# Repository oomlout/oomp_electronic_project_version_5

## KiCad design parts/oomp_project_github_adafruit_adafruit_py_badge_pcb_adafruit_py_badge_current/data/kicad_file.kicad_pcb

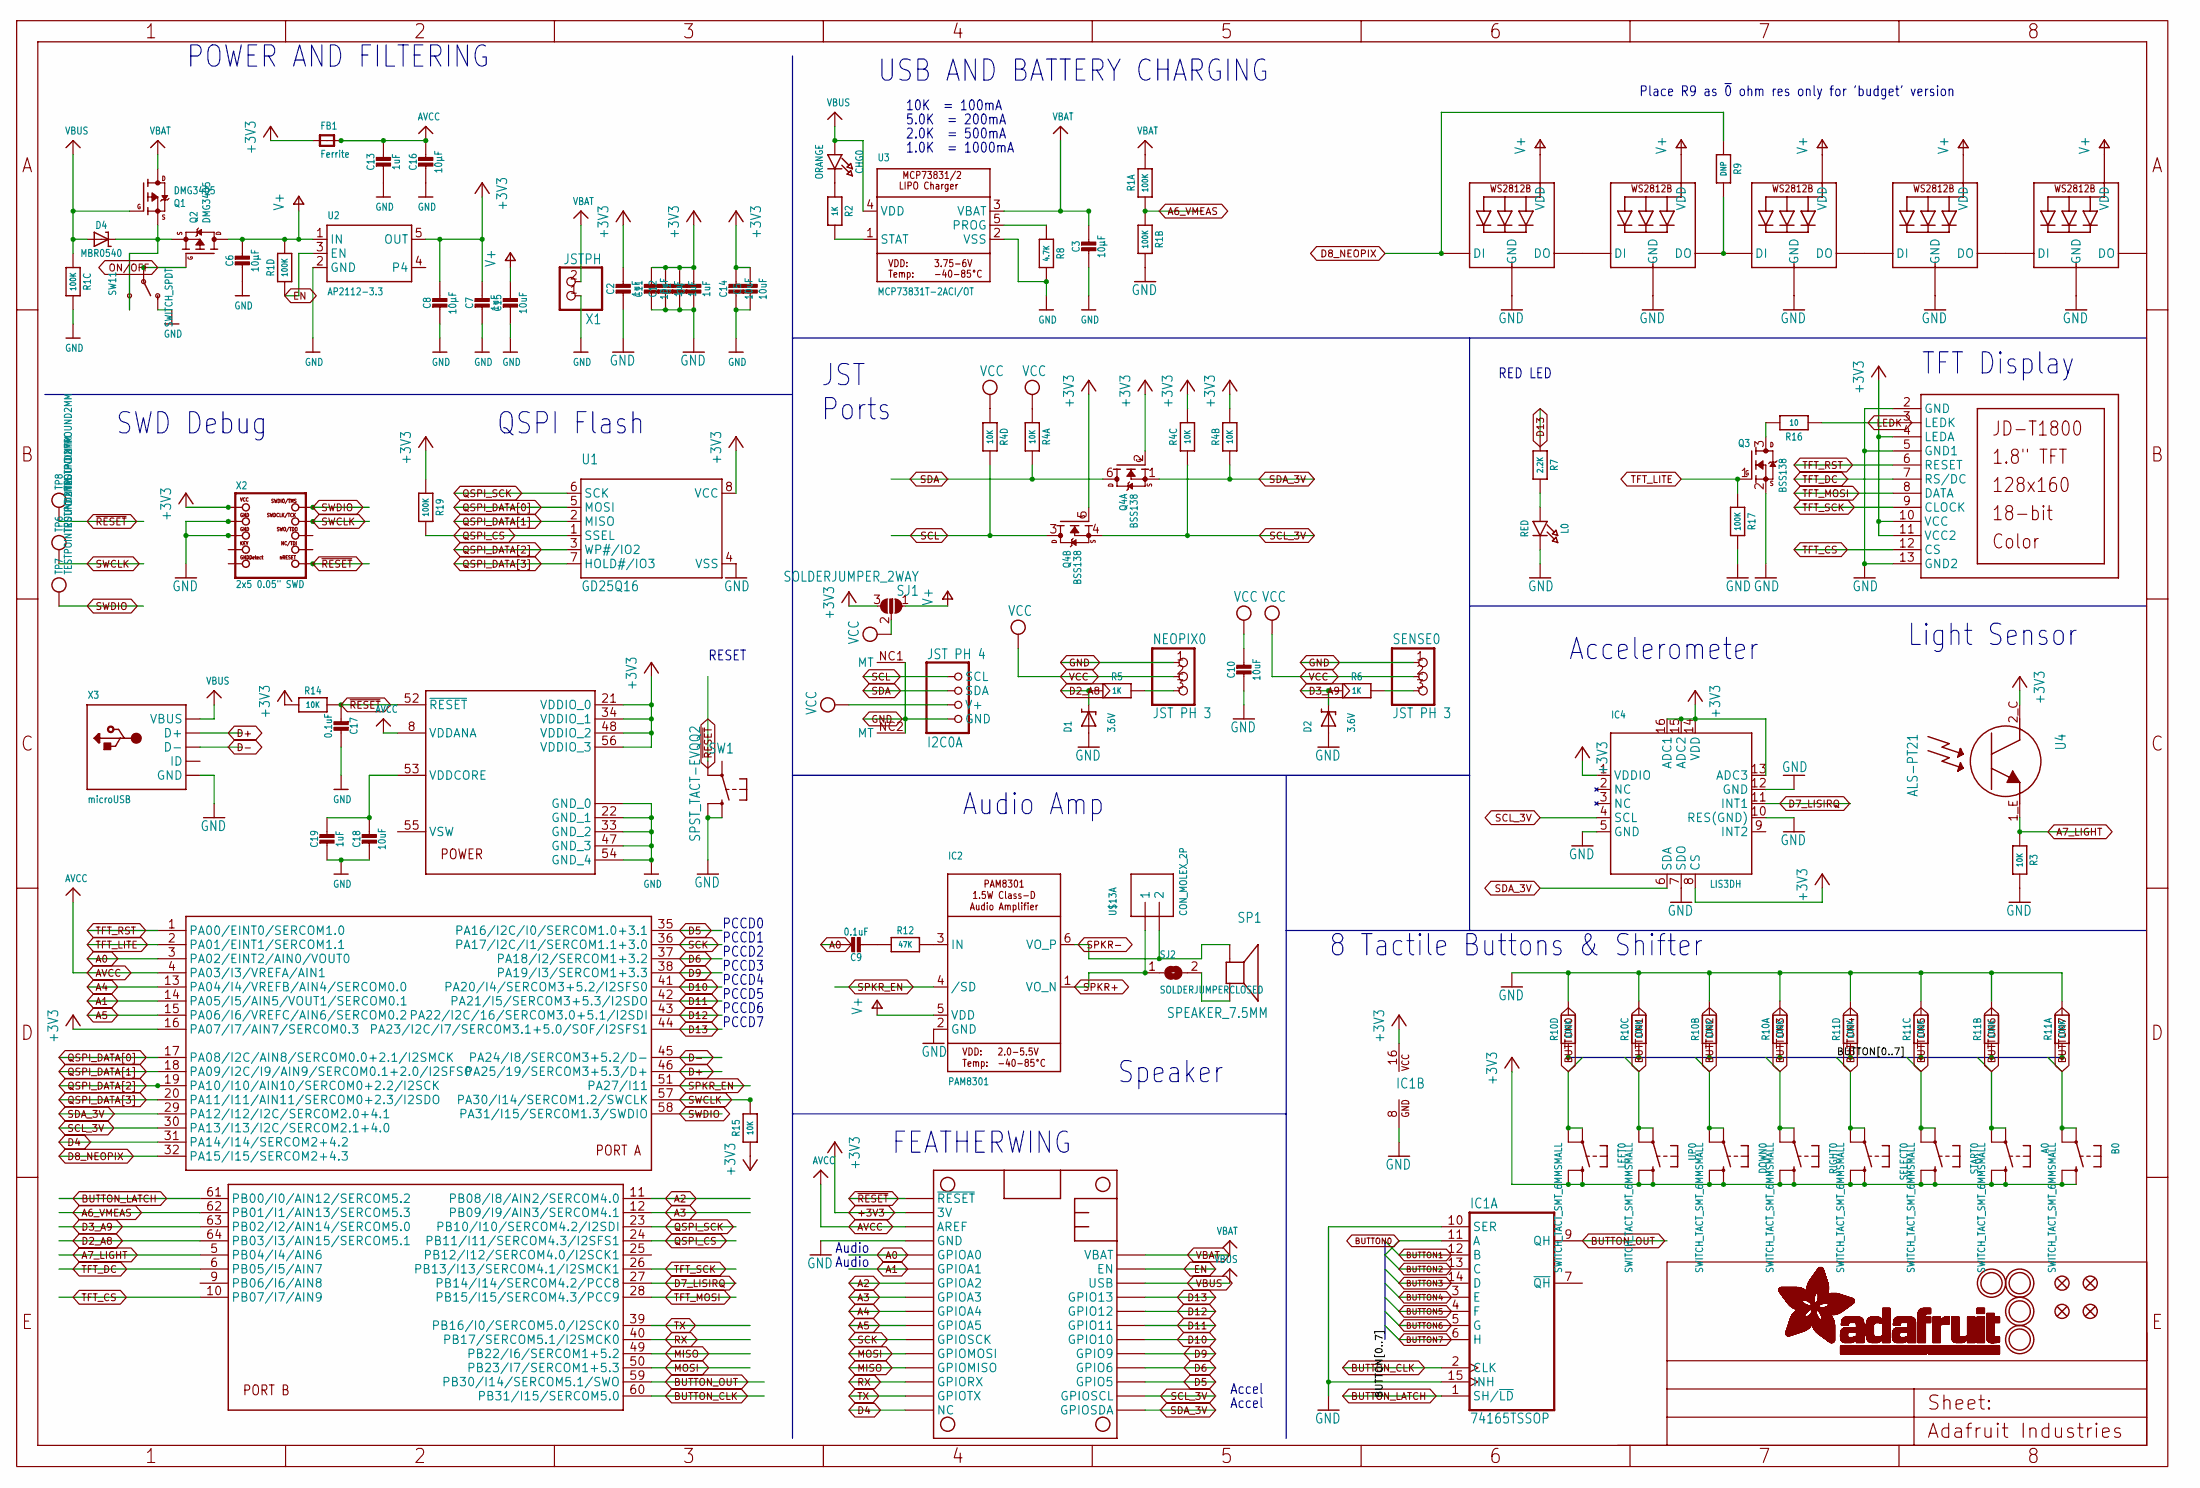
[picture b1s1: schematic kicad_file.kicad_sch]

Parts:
A0: SWITCH_TACT_SMT_6MMSMALL; 6MM_SMT
B0: SWITCH_TACT_SMT_6MMSMALL; 6MM_SMT
C1, C2, C4, C7, C12, C13, C19: 1uF; 0603-NO
C3, C6, C8: 10µF; 0805-NO
C5, C10, C11, C14, C15, C18: 10uF; 0805-NO
C9, C17: 0.1uF; 0603-NO
C16: 10µF; _0805MP
CHG0: ORANGE; CHIPLED_0805_NOOUTLINE
D1, D2: 3.6V; SOD-323
D4: MBR0540; SOD-123
DOWN0: SWITCH_TACT_SMT_6MMSMALL; 6MM_SMT
FB1: Ferrite; 0805-NO
I2C0: JST PH 4; JSTPH4
IC1: 74165TSSOP; TSSOP16
IC2: PAM8301; SOT23-6
IC4: LIS3DH; LGA16_3X3MM
L0: RED; CHIPLED_0805_NOOUTLINE
LCD1: DISP_LCD_JDT1800; JD-T1800
LED1, LED2, LED3, LED4, LED5: WS2812B3535; LED3535
LEFT0: SWITCH_TACT_SMT_6MMSMALL; 6MM_SMT
MS1: FEATHERWING_SMTDUALNOHOLES; FEATHERWING_SMT_NOHOLES
NEOPIX0: JST PH 3; JSTPH3
Q1, Q2: DMG3405; SOT23-R
Q3: BSS138; SOT23-WIDE
Q4: BSS138; SOT363
R1, R10, R11: 100K; RESPACK_4X0603
R2, R5, R6: 1K; 0603-NO
R3, R14, R15: 10K; 0603-NO
R4: 10K; RESPACK_4X0603
R7: 2.2K; 0603-NO
R8: 4.7K; 0603-NO
R9: DNP; 0603-NO
R12: 47K; 0603-NO
R16: 10; 0603-NO
R17, R19: 100K; 0603-NO
RIGHT0: SWITCH_TACT_SMT_6MMSMALL; 6MM_SMT
SELECT0: SWITCH_TACT_SMT_6MMSMALL; 6MM_SMT
SENSE0: JST PH 3; JSTPH3
SJ1: SOLDERJUMPER_2WAY; SOLDERJUMPER_2WAY_OPEN_NOPASTE
SJ2: SOLDERJUMPERCLOSED; SOLDERJUMPER_CLOSEDWIRE
SP1: SPEAKER_7.5MM; BUZZER_SMT_7.5MM
START0: SWITCH_TACT_SMT_6MMSMALL; 6MM_SMT
SW1: SPST_TACT-EVQQ2; EVQ-Q2_SMALLER
SW11: SWITCH_SPDT; SPDT_SMT_SSSS811101
TP6, TP7, TP8: TESTPOINTROUND2MM; TESTPOINT_ROUND_2MM
U1: GD25Q16; SOIC8_208MIL
U2: AP2112-3.3; SOT23-5
U3: MCP73831T-2ACI/OT; SOT23-5
U4: ALS-PT21; ALS-PT26-21C
U$5, U$6, U$15, U$17: MOUNTINGHOLE3.0THIN; MOUNTINGHOLE_3.0_PLATEDTHIN
U$13: CON_MOLEX_2P; 53398-0271
U$24: ATSAMD51J19; PQFN64-1
U$34, U$35, U$42, U$43: FIDUCIAL_1MM
UP0: SWITCH_TACT_SMT_6MMSMALL; 6MM_SMT
X1: JSTPH; JSTPH2
X2: 2x5 0.05" SWD; 2X05_1.27MM_BOX_POSTS
X3: microUSB; 4UCONN_20329_V2

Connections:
+3V3: A0.B (S), A0.B' (S1), B0.B (S), B0.B' (S1), C1.1, C2.1, C4.1, C5.1, C7.1, C8.1, C11.1, C12.1, C14.1, DOWN0.B (S), DOWN0.B' (S1), FB1.1, IC1.16 (VCC), IC4.1 (VDDIO), IC4.8 (CS), IC4.13 (ADC3), IC4.14 (VDD), IC4.15 (ADC2), IC4.16 (ADC1), LCD1.4 (LEDA), LCD1.10 (VCC), LCD1.11 (VCC2), LEFT0.B (S), LEFT0.B' (S1), MS1.2 (3V), MS1.2B (3V), Q4.2 (G), Q4.5 (G), R4.2 (1), R4.3 (1), R14.1, R15.1, R19.1, RIGHT0.B (S), RIGHT0.B' (S1), SELECT0.B (S), SELECT0.B' (S1), SJ1.3, START0.B (S), START0.B' (S1), U1.8 (VCC), U2.5 (OUT), U4.2_C (C), U$24.16 (PA07/I7/AIN7/SERCOM0.3), U$24.21 (VDDIO_0), U$24.34 (VDDIO_1), U$24.48 (VDDIO_2), U$24.56 (VDDIO_3), UP0.B (S), UP0.B' (S1), X2.1 (VCC)
A0: C9.1, MS1.5 (GPIOA0), MS1.5B (GPIOA0), U$24.3 (PA02/EINT2/AIN0/VOUT0)
A1: MS1.6 (GPIOA1), MS1.6B (GPIOA1), U$24.14 (PA05/I5/AIN5/VOUT1/SERCOM0.1)
A2: MS1.7 (GPIOA2), MS1.7B (GPIOA2), U$24.11 (PB08/I8/AIN2/SERCOM4.0)
A3: MS1.8 (GPIOA3), MS1.8B (GPIOA3), U$24.12 (PB09/I9/AIN3/SERCOM4.1)
A4: MS1.9 (GPIOA4), MS1.9B (GPIOA4), U$24.13 (PA04/I4/VREFB/AIN4/SERCOM0.0)
A5: MS1.10 (GPIOA5), MS1.10B (GPIOA5), U$24.15 (PA06/I6/VREFC/AIN6/SERCOM0.2)
A6_VMEAS: R1.1, R1.2 (1), U$24.62 (PB01/I1/AIN13/SERCOM5.3)
A7_LIGHT: R3.2, U4.1_E (E), U$24.5 (PB04/I4/AIN6)
AVCC: C13.1, C16.1, FB1.2, MS1.3 (AREF), MS1.3B (AREF), U$24.4 (PA03/I3/VREFA/AIN1), U$24.8 (VDDANA)
BUTTON0: IC1.11 (A), LEFT0.A, LEFT0.A' (P1), R10.4 (1)
BUTTON1: IC1.12 (B), R10.3 (1), UP0.A, UP0.A' (P1)
BUTTON2: DOWN0.A, DOWN0.A' (P1), IC1.13 (C), R10.2 (1)
BUTTON3: IC1.14 (D), R10.1, RIGHT0.A, RIGHT0.A' (P1)
BUTTON4: IC1.3 (E), R11.4 (1), SELECT0.A, SELECT0.A' (P1)
BUTTON5: IC1.4 (F), R11.3 (1), START0.A, START0.A' (P1)
BUTTON6: A0.A, A0.A' (P1), IC1.5 (G), R11.2 (1)
BUTTON7: B0.A, B0.A' (P1), IC1.6 (H), R11.1
BUTTON_CLK: IC1.2 (CLK), U$24.60 (PB31/I15/SERCOM5.0)
BUTTON_LATCH: IC1.1 (SH/~LD), U$24.61 (PB00/I0/AIN12/SERCOM5.2)
BUTTON_OUT: IC1.9 (QH), U$24.59 (PB30/I14/SERCOM5.1/SWO)
CHG_LED: R2.2, U3.1 (STAT)
CHG_RATE: R8.1, U3.5 (PROG)
D2_: NEOPIX0.3, R5.1
D2_A8: D1.C, R5.2, U$24.64 (PB03/I3/AIN15/SERCOM5.1)
D3_: R6.1, SENSE0.3
D3_A9: D2.C, R6.2, U$24.63 (PB02/I2/AIN14/SERCOM5.0)
D4: MS1.16 (NC), MS1.16B (NC), U$24.31 (PA14/I14/SERCOM2+4.2)
D5: MS1.19 (GPIO5), MS1.19B (GPIO5), U$24.35 (PA16/I2C/I0/SERCOM1.0+3.1)
D6: MS1.20 (GPIO6), MS1.20B (GPIO6), U$24.37 (PA18/I2/SERCOM1+3.2)
D7_LISIRQ: IC4.11 (INT1), U$24.27 (PB14/I14/SERCOM4.2/PCC8)
D8_NEOPIX: LED1.1 (DI), R9.1, U$24.32 (PA15/I15/SERCOM2+4.3)
D9: MS1.21 (GPIO9), MS1.21B (GPIO9), U$24.38 (PA19/I3/SERCOM1+3.3)
D10: MS1.22 (GPIO10), MS1.22B (GPIO10), U$24.41 (PA20/I4/SERCOM3+5.2/I2SFS0)
D11: MS1.23 (GPIO11), MS1.23B (GPIO11), U$24.42 (PA21/I5/SERCOM3+5.3/I2SDO)
D12: MS1.24 (GPIO12), MS1.24B (GPIO12), U$24.43 (PA22/I2C/16/SERCOM3.0+5.1/I2SDI)
D13: MS1.25 (GPIO13), MS1.25B (GPIO13), R7.1, U$24.44 (PA23/I2C/I7/SERCOM3.1+5.0/SOF/I2SFS1)
D+: U$24.46 (PA25/19/SERCOM3+5.3/D+), X3.D+
D-: U$24.45 (PA24/I8/SERCOM3+5.2/D-), X3.D-
EN: MS1.27 (EN), MS1.27B (EN), R1.4 (1), U2.3 (EN)
GND: C1.2, C2.2, C3.2, C4.2, C5.2, C6.2, C7.2, C8.2, C10.2, C11.2, C12.2, C13.2, C14.2, C15.2, C16.2, C17.1, C18.2, C19.2, D1.A, D2.A, I2C0.1 (GND), I2C0.NC1 (MT), I2C0.NC2 (MT), IC1.8 (GND), IC1.10 (SER), IC1.15 (INH), IC2.2 (GND), IC4.5 (GND), IC4.7 (SDO), IC4.10 (RES(GND)), IC4.12 (GND), L0.C, LCD1.2 (GND), LCD1.5 (GND1), LCD1.13 (GND2), LED1.4 (GND), LED2.4 (GND), LED3.4 (GND), LED4.4 (GND), LED5.4 (GND), MS1.4 (GND), MS1.4B (GND), NEOPIX0.1, Q3.2 (S), R1.6 (2), R1.7 (2), R3.1, R8.2, R10.5 (2), R10.6 (2), R10.7 (2), R10.8 (2), R11.5 (2), R11.6 (2), R11.7 (2), R11.8 (2), R17.2, SENSE0.1, SW1.B (S), SW1.B' (S1), SW11.A (O), U1.4 (VSS), U2.2 (GND), U3.2 (VSS), U$24.7 (GND_0), U$24.22 (GND_1), U$24.33 (GND_2), U$24.47 (GND_3), U$24.54 (GND_4), U$24.EXP (GND_0), X1.1, X2.3 (GND), X2.5 (GND), X3.BASE@1 (GND), X3.BASE@2 (GND), X3.GND, X3.SPRT@1 (GND), X3.SPRT@2 (GND), X3.SPRT@3 (GND), X3.SPRT@4 (GND)
LEDK: LCD1.3 (LEDK), R16.1
MISO: MS1.13 (GPIOMISO), MS1.13B (GPIOMISO), U$24.49 (PB22/I6/SERCOM1+5.2)
MOSI: MS1.12 (GPIOMOSI), MS1.12B (GPIOMOSI), U$24.50 (PB23/I7/SERCOM1+5.3)
unnamed: CHG0.C, R2.1
unnamed: L0.A, R7.2
unnamed: LED1.3 (DO), LED2.1 (DI)
unnamed: LED2.3 (DO), LED3.1 (DI), R9.2
unnamed: LED3.3 (DO), LED4.1 (DI)
unnamed: Q3.3 (D), R16.2
unnamed: LED4.3 (DO), LED5.1 (DI)
unnamed: D4.C, Q1.2 (S), Q2.2 (S), SW11.C (S)
unnamed: C9.2, R12.1
unnamed: IC2.3 (IN), R12.2
unnamed: SJ2.2, SP1.-
ON/OFF: Q2.1 (G), SW11.B
QSPI_CS: R19.2, U1.1 (SSEL), U$24.24 (PB11/I11/SERCOM4.3/I2SFS1)
QSPI_DATA[0]: U1.5 (MOSI), U$24.17 (PA08/I2C/AIN8/SERCOM0.0+2.1/I2SMCK)
QSPI_DATA[1]: U1.2 (MISO), U$24.18 (PA09/I2C/I9/AIN9/SERCOM0.1+2.0/I2SFS0)
QSPI_DATA[2]: U1.3 (WP#/IO2), U$24.19 (PA10/I10/AIN10/SERCOM0+2.2/I2SCK)
QSPI_DATA[3]: U1.7 (HOLD#/IO3), U$24.20 (PA11/I11/AIN11/SERCOM0+2.3/I2SDO)
QSPI_SCK: U1.6 (SCK), U$24.23 (PB10/I10/SERCOM4.2/I2SDI)
RX: MS1.14 (GPIORX), MS1.14B (GPIORX), U$24.40 (PB17/SERCOM5.1/I2SMCK0)
SCK: MS1.11 (GPIOSCK), MS1.11B (GPIOSCK), U$24.36 (PA17/I2C/I1/SERCOM1.1+3.0)
SCL: I2C0.4 (SCL), Q4.3 (D), R4.5 (2)
SCL_3V: IC4.4 (SCL), MS1.18 (GPIOSCL), MS1.18B (GPIOSCL), Q4.4 (S), R4.6 (2), U$24.30 (PA13/I13/I2C/SERCOM2.1+4.0)
SDA: I2C0.3 (SDA), Q4.6 (D), R4.8 (2)
SDA_3V: IC4.6 (SDA), MS1.17 (GPIOSDA), MS1.17B (GPIOSDA), Q4.1 (S), R4.7 (2), U$24.29 (PA12/I12/I2C/SERCOM2.0+4.1)
SPKR+: IC2.1 (VO_N), SJ2.1, U$13.1
SPKR-: IC2.6 (VO_P), SP1.+, U$13.2
SPKR_EN: IC2.4 (/SD), U$24.51 (PA27/I11)
SWCLK: R15.2, TP6.P$1, U$24.57 (PA30/I14/SERCOM1.2/SWCLK), X2.4 (SWDCLK)
SWDIO: TP7.P$1, U$24.58 (PA31/I15/SERCOM1.3/SWDIO), X2.2 (SWDIO)
TFT_CS: LCD1.12 (CS), U$24.10 (PB07/I7/AIN9)
TFT_DC: LCD1.7 (RS/DC), U$24.6 (PB05/I5/AIN7)
TFT_LITE: Q3.1 (G), R17.1, U$24.2 (PA01/EINT1/SERCOM1.1)
TFT_MOSI: LCD1.8 (DATA), U$24.28 (PB15/I15/SERCOM4.3/PCC9)
TFT_RST: LCD1.6 (RESET), U$24.1 (PA00/EINT0/SERCOM1.0)
TFT_SCK: LCD1.9 (CLOCK), U$24.26 (PB13/I13/SERCOM4.1/I2SMCK1)
TX: MS1.15 (GPIOTX), MS1.15B (GPIOTX), U$24.39 (PB16/I0/SERCOM5.0/I2SCK0)
V+: C6.1, C15.1, IC2.5 (VDD), LED1.2 (VDD), LED2.2 (VDD), LED3.2 (VDD), LED4.2 (VDD), LED5.2 (VDD), Q2.3 (D), R1.5 (2), SJ1.1, U2.1 (IN)
VBAT: C3.1, MS1.28 (VBAT), MS1.28B (VBAT), Q1.3 (D), R1.8 (2), U3.3 (VBAT), X1.2
VBUS: CHG0.A, D4.A, MS1.26 (USB), MS1.26B (USB), Q1.1 (G), R1.3 (1), U3.4 (VDD), X3.VBUS
VCC: C10.1, I2C0.2 (V+), NEOPIX0.2, R4.1, R4.4 (1), SENSE0.2, SJ1.2
VDDCORE2: C18.1, C19.1, U$24.53 (VDDCORE)
~RESET: C17.2, MS1.1 (~RESET), MS1.1B (~RESET), R14.2, SW1.A' (P1), TP8.P$1, U$24.52 (~RESET), X2.10 (NRESET)

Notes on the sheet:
PCCD6
PCCD3
Place R9 as ~{0} ohm res only for 'budget' version
10K = 100mA
PCCD2
SWD Debug
Audio Amp
Accel
QSPI Flash
USB AND BATTERY CHARGING
JST Ports
FEATHERWING
1.0K = 1000mA
Speaker
8 Tactile Buttons & Shifter
5.0K = 200mA
Audio
PCCD5
PCCD7
Light Sensor
2.0K = 500mA
PCCD4
RED LED
PCCD1
Accelerometer
TFT Display
RESET
POWER AND FILTERING
PCCD0

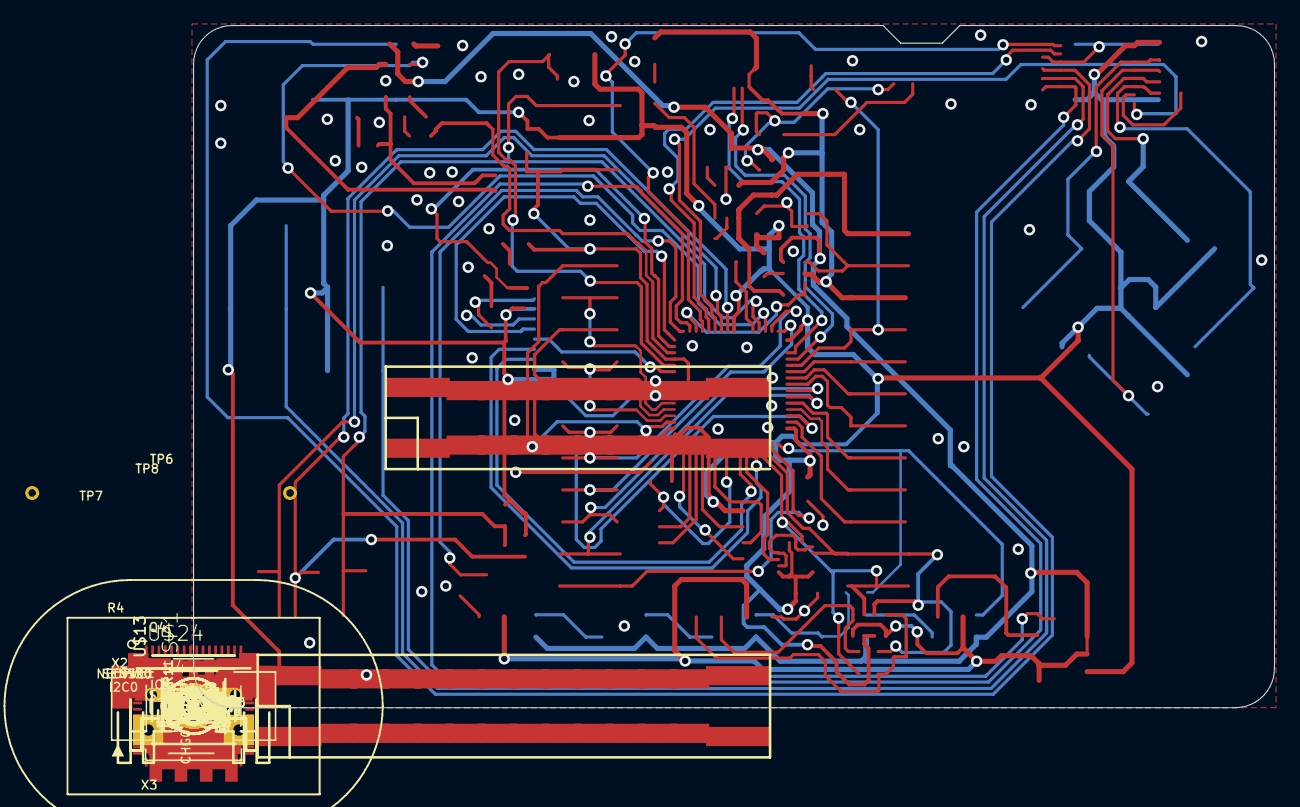
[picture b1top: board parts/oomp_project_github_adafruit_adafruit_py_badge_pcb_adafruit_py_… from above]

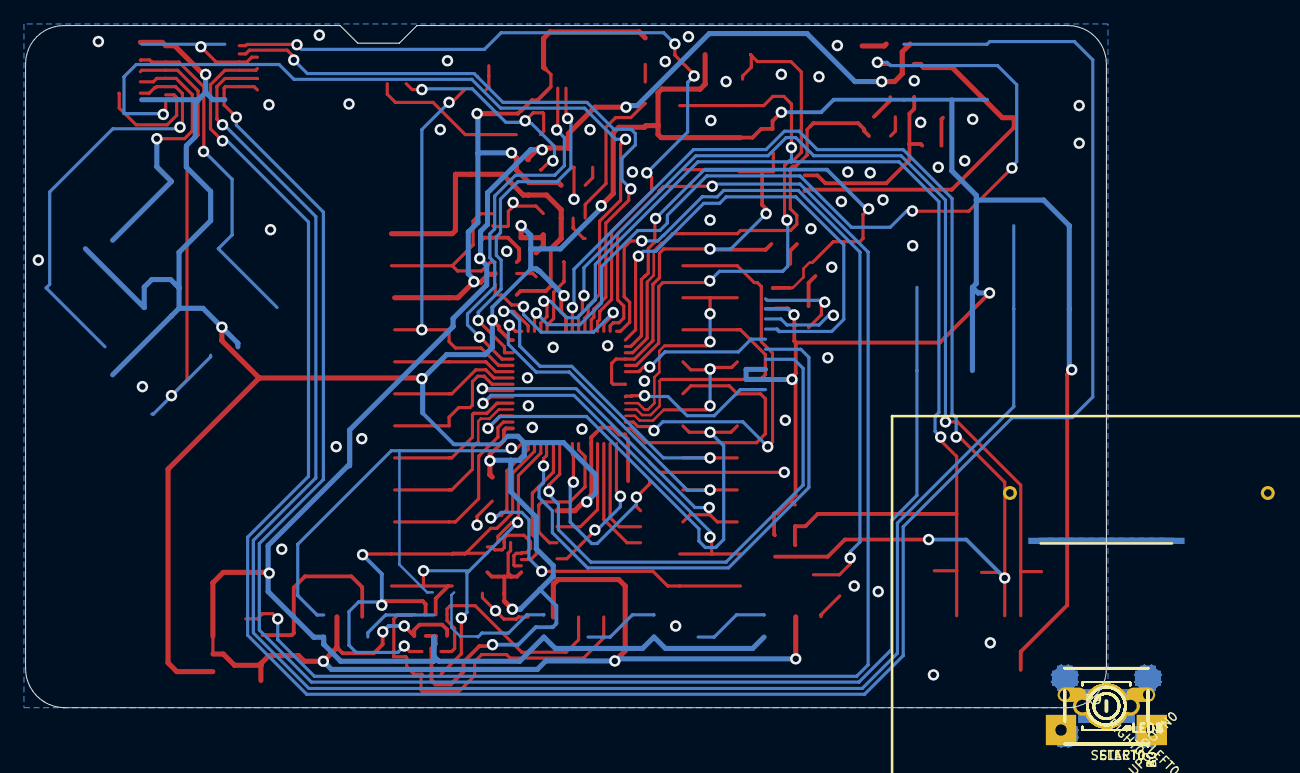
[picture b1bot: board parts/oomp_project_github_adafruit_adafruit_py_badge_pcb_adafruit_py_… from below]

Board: 2 copper layers, 85.7 x 54.1 mm, 96 parts (18 on the bottom side), 86 nets.

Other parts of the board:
U$8: SPEAKER_OVAL8OHM
U$18: PYBADGE_TOP
U$32: PYBADGE_BOT
U$37: PCBFEAT-REV-040

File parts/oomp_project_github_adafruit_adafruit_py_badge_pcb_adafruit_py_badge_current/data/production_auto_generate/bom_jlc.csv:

Comment,Designator,Footprint,LCSC Part #
,"A0,B0,DOWN0,LEFT0,RIGHT0,SELECT0,START0,UP0",Adafruit PyBadge-import-fps:6MM_SMT,
,U$37,Adafruit PyBadge-import-fps:PCBFEAT-REV-040,
,U$32,Adafruit PyBadge-import-fps:PYBADGE_BOT,
,U$18,Adafruit PyBadge-import-fps:PYBADGE_TOP,
,SW11,Adafruit PyBadge-import-fps:SPDT_SMT_SSSS811101,
,U$8,Adafruit PyBadge-import-fps:SPEAKER_OVAL8OHM,
,"TP6,TP7,TP8",Adafruit PyBadge-import-fps:TESTPOINT_ROUND_2MM,
0.1uF,"C9,C17",Adafruit PyBadge-import-fps:0603-NO,C14663
10,R16,Adafruit PyBadge-import-fps:0603-NO,C22859
100K,"R17,R19",Adafruit PyBadge-import-fps:0603-NO,C25803
100K,"R1,R10,R11",Adafruit PyBadge-import-fps:RESPACK_4X0603,C25803
10K,"R3,R14,R15",Adafruit PyBadge-import-fps:0603-NO,C98220
10K,R4,Adafruit PyBadge-import-fps:RESPACK_4X0603,C98220
10uF,"C5,C10,C11,C14,C15,C18",Adafruit PyBadge-import-fps:0805-NO,
10µF,"C3,C6,C8",Adafruit PyBadge-import-fps:0805-NO,
10µF,C16,Adafruit PyBadge-import-fps:_0805MP,
1K,"R2,R5,R6",Adafruit PyBadge-import-fps:0603-NO,C2907002
1uF,"C1,C2,C4,C7,C12,C13,C19",Adafruit PyBadge-import-fps:0603-NO,C5673
2.2K,R7,Adafruit PyBadge-import-fps:0603-NO,C4190
"2x5 0.05"" SWD",X2,Adafruit PyBadge-import-fps:2X05_1.27MM_BOX_POSTS,
3.6V,"D1,D2",Adafruit PyBadge-import-fps:SOD-323,
4.7K,R8,Adafruit PyBadge-import-fps:0603-NO,C23162
47K,R12,Adafruit PyBadge-import-fps:0603-NO,C2907042
74165TSSOP,IC1,Adafruit PyBadge-import-fps:TSSOP16,
ALS-PT21,U4,Adafruit PyBadge-import-fps:ALS-PT26-21C,
AP2112-3.3,U2,Adafruit PyBadge-import-fps:SOT23-5,
ATSAMD51J19,U$24,Adafruit PyBadge-import-fps:PQFN64-1,
BSS138,Q3,Adafruit PyBadge-import-fps:SOT23-WIDE,C52895
BSS138,Q4,Adafruit PyBadge-import-fps:SOT363,
CON_MOLEX_2P,U$13,Adafruit PyBadge-import-fps:53398-0271,
DISP_LCD_JDT1800,LCD1,Adafruit PyBadge-import-fps:JD-T1800,
DMG3405,"Q1,Q2",Adafruit PyBadge-import-fps:SOT23-R,
DNP,R9,Adafruit PyBadge-import-fps:0603-NO,
FEATHERWING_SMTDUALNOHOLES,MS1,Adafruit PyBadge-import-fps:FEATHERWING_SMT_NOHOLES,
Ferrite,FB1,Adafruit PyBadge-import-fps:0805-NO,
FIDUCIAL_1MM,"U$34,U$35,U$42,U$43",Adafruit PyBadge-import-fps:FIDUCIAL_1MM,
GD25Q16,U1,Adafruit PyBadge-import-fps:SOIC8_208MIL,
JST PH 3,"NEOPIX0,SENSE0",Adafruit PyBadge-import-fps:JSTPH3,
JST PH 4,I2C0,Adafruit PyBadge-import-fps:JSTPH4,
JSTPH,X1,Adafruit PyBadge-import-fps:JSTPH2,
LIS3DH,IC4,Adafruit PyBadge-import-fps:LGA16_3X3MM,
MBR0540,D4,Adafruit PyBadge-import-fps:SOD-123,
MCP73831T-2ACI/OT,U3,Adafruit PyBadge-import-fps:SOT23-5,
microUSB,X3,Adafruit PyBadge-import-fps:4UCONN_20329_V2,
ORANGE,CHG0,Adafruit PyBadge-import-fps:CHIPLED_0805_NOOUTLINE,
PAM8301,IC2,Adafruit PyBadge-import-fps:SOT23-6,
RED,L0,Adafruit PyBadge-import-fps:CHIPLED_0805_NOOUTLINE,
SPEAKER_7.5MM,SP1,Adafruit PyBadge-import-fps:BUZZER_SMT_7.5MM,
SPST_TACT-EVQQ2,SW1,Adafruit PyBadge-import-fps:EVQ-Q2_SMALLER,
WS2812B3535,"LED1,LED2,LED3,LED4,LED5",Adafruit PyBadge-import-fps:LED3535,

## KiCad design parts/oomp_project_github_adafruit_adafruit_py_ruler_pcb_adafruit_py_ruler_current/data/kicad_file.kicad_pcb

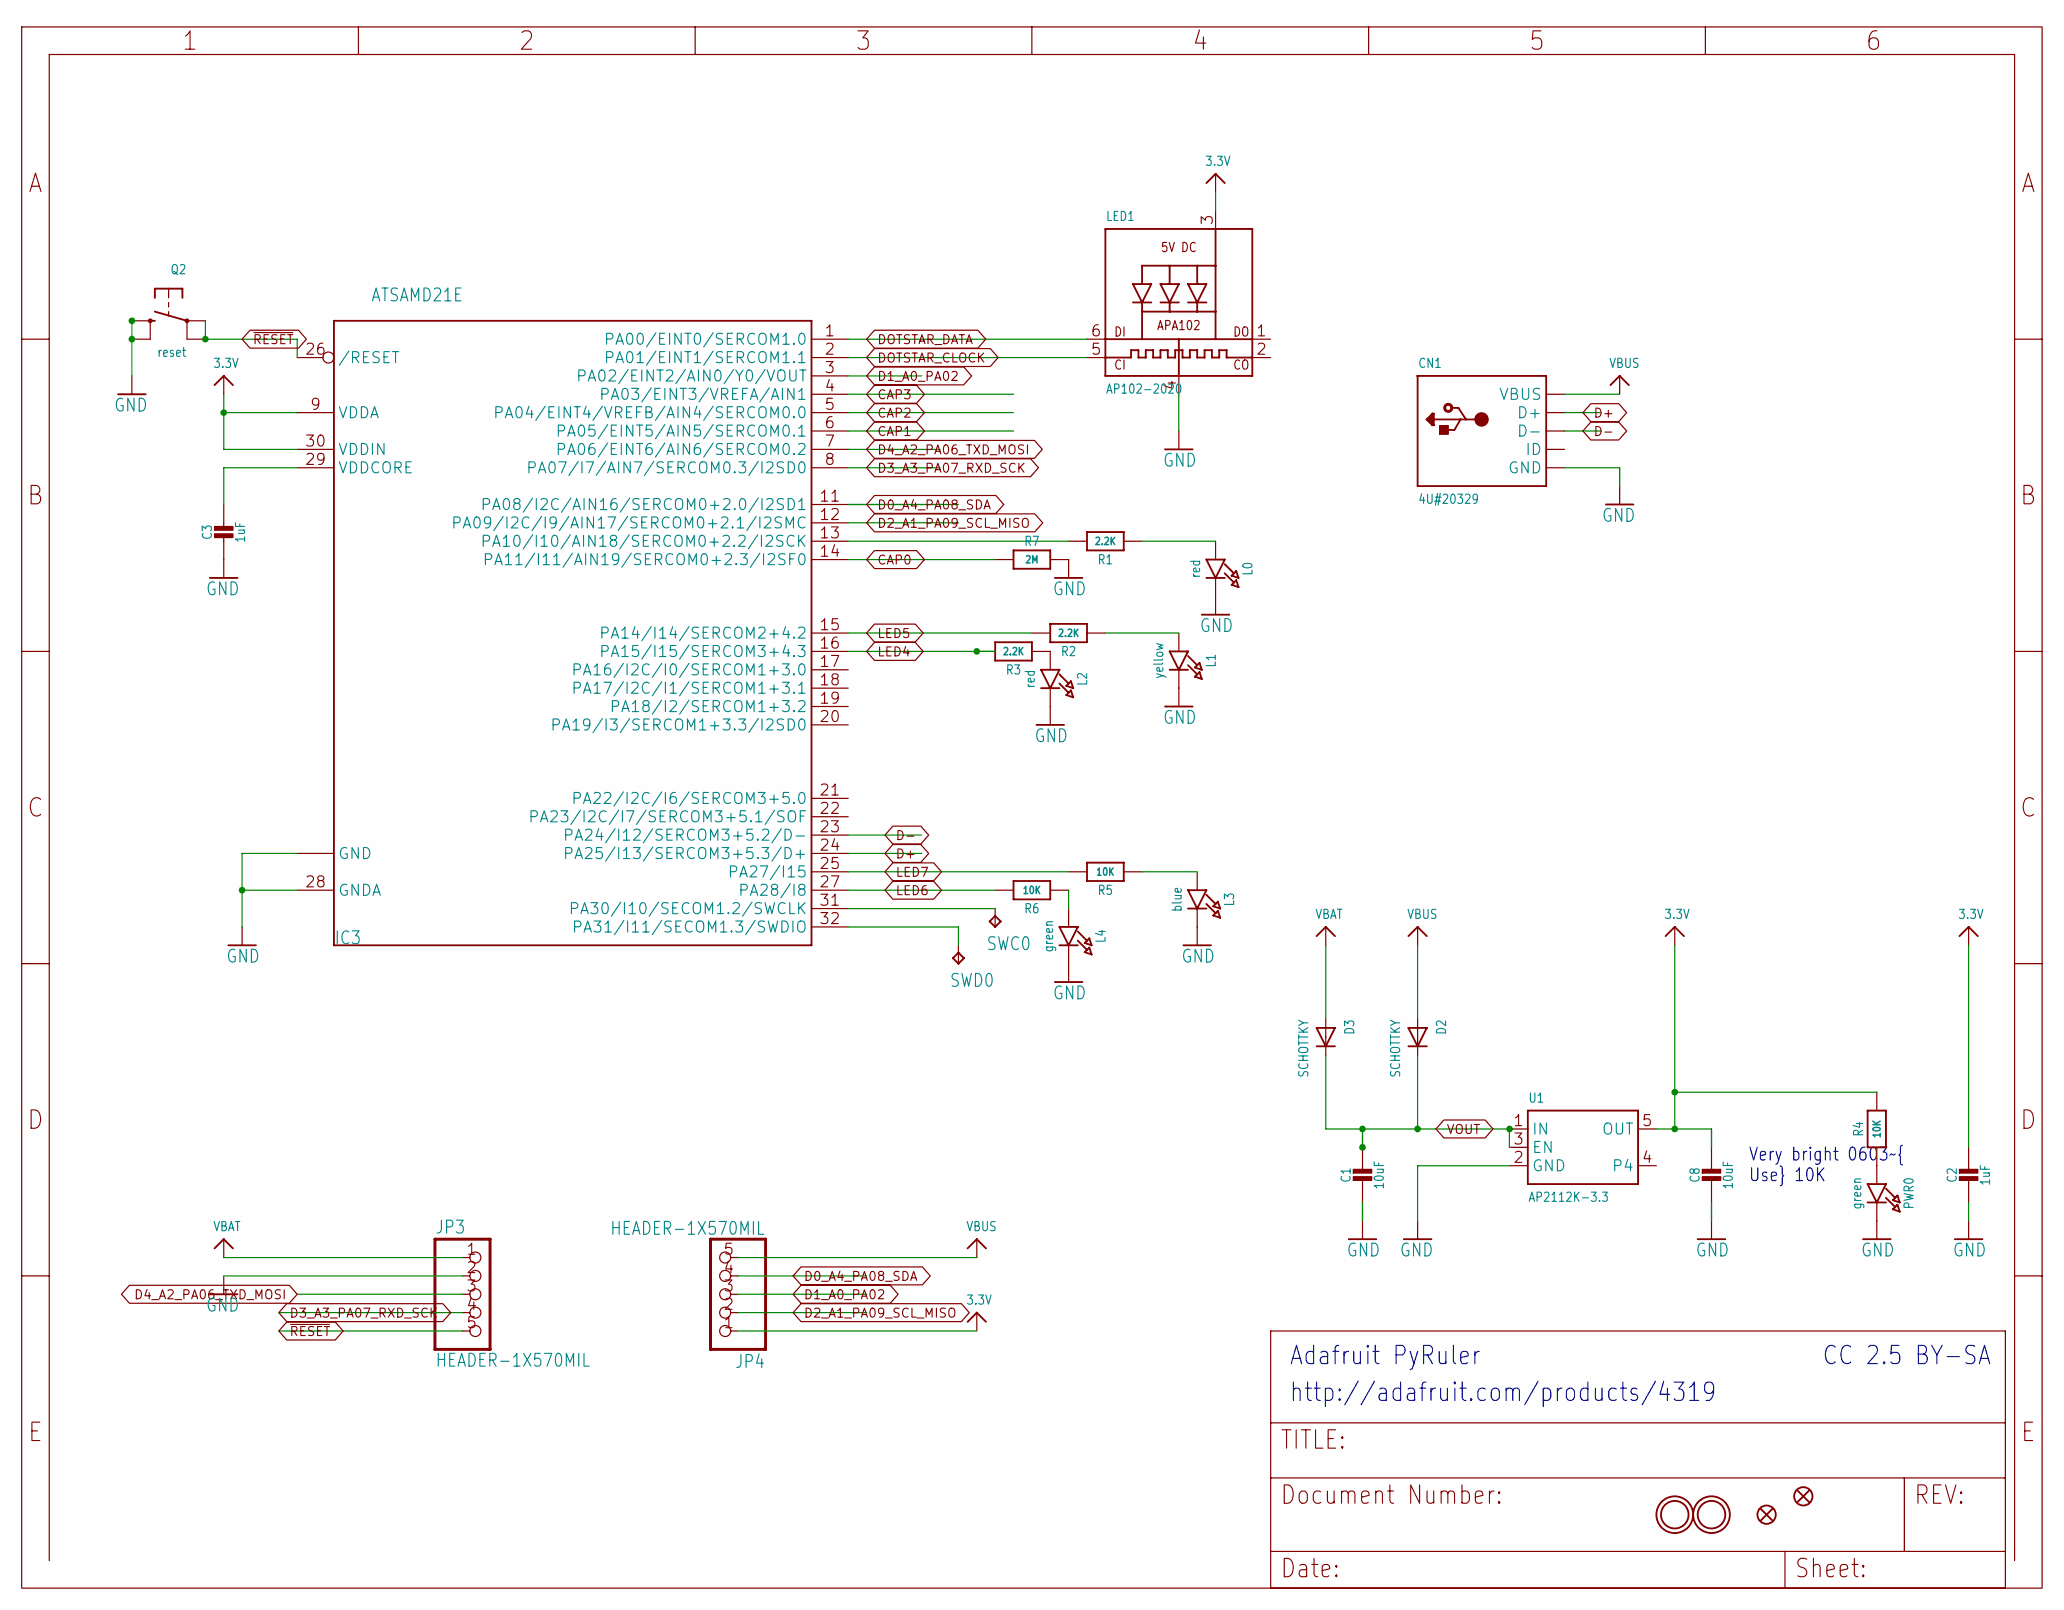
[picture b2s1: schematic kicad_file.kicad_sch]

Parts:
C1, C8: 10uF; 0805-NO
C2, C3: 1uF; 0603-NO
CN1: 4U#20329; 4UCONN_20329_NARROW
D2, D3: SCHOTTKY; SOD-123FL
IC3: ATSAMD21E; QFN32_5MM
JP3, JP4: HEADER-1X570MIL; 1X05_ROUND_70
L0, L2: red; CHIPLED_0603_NOOUTLINE
L1: yellow; CHIPLED_0603_NOOUTLINE
L3: blue; CHIPLED_0603_NOOUTLINE
L4: green; CHIPLED_0603_NOOUTLINE
LED1: AP102-2020; APA102_2020
PWR0: green; CHIPLED_0603_NOOUTLINE
Q2: reset; BTN_KMR2_4.6X2.8
R1, R2, R3: 2.2K; 0603-NO
R4, R5, R6: 10K; 0603-NO
R7: 2M; 0603-NO
SWC0: TPB1,27; B1,27
SWD0: TPB1,27; B1,27
U1: AP2112K-3.3; SOT23-5
U$1, U$6: FIDUCIAL_1MM
U$8, U$9: MOUNTINGHOLE2.0; MOUNTINGHOLE_2.0_PLATED

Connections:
3.3V: C2.1, C8.1, IC3.9 (VDDA), IC3.30 (VDDIN), JP4.1, LED1.3 (VDD), R4.2, U1.5 (OUT)
CAP0: IC3.14 (PA11/I11/AIN19/SERCOM0+2.3/I2SF0), R7.1
CAP1: IC3.6 (PA05/EINT5/AIN5/SERCOM0.1)
CAP2: IC3.5 (PA04/EINT4/VREFB/AIN4/SERCOM0.0)
CAP3: IC3.4 (PA03/EINT3/VREFA/AIN1)
D0_A4_PA08_SDA: IC3.11 (PA08/I2C/AIN16/SERCOM0+2.0/I2SD1), JP4.4
D1_A0_PA02: IC3.3 (PA02/EINT2/AIN0/Y0/VOUT), JP4.3
D2_A1_PA09_SCL_MISO: IC3.12 (PA09/I2C/I9/AIN17/SERCOM0+2.1/I2SMC), JP4.2
D3_A3_PA07_RXD_SCK: IC3.8 (PA07/I7/AIN7/SERCOM0.3/I2SD0), JP3.4
D4_A2_PA06_TXD_MOSI: IC3.7 (PA06/EINT6/AIN6/SERCOM0.2), JP3.3
D+: CN1.D+, IC3.24 (PA25/I13/SERCOM3+5.3/D+)
D-: CN1.D-, IC3.23 (PA24/I12/SERCOM3+5.2/D-)
DOTSTAR_CLOCK: IC3.2 (PA01/EINT1/SERCOM1.1), LED1.5 (CKI)
DOTSTAR_DATA: IC3.1 (PA00/EINT0/SERCOM1.0), LED1.6 (DI)
GND: C1.2, C2.2, C3.2, C8.2, CN1.BASE@1 (GND), CN1.BASE@2 (GND), CN1.GND, CN1.SPRT@1 (GND), CN1.SPRT@2 (GND), CN1.SPRT@3 (GND), CN1.SPRT@4 (GND), IC3.10 (GND), IC3.28 (GNDA), IC3.33 (GND), JP3.2, L0.C, L1.C, L2.C, L3.C, L4.C, LED1.4 (GND), PWR0.C, Q2.B (S), Q2.B' (S1), R7.2, U1.2 (GND)
LED: IC3.13 (PA10/I10/AIN18/SERCOM0+2.2/I2SCK), R1.2
LED4: IC3.16 (PA15/I15/SERCOM3+4.3), R3.2
LED5: IC3.15 (PA14/I14/SERCOM2+4.2), R2.2
LED6: IC3.27 (PA28/I8), R6.2
LED7: IC3.25 (PA27/I15), R5.2
unnamed: L0.A, R1.1
unnamed: IC3.31 (PA30/I10/SECOM1.2/SWCLK), SWC0.TP
unnamed: IC3.32 (PA31/I11/SECOM1.3/SWDIO), SWD0.TP
unnamed: PWR0.A, R4.1
unnamed: L1.A, R2.1
unnamed: L2.A, R3.1
unnamed: L4.A, R6.1
unnamed: L3.A, R5.1
VBAT: D3.A, JP3.1
VBUS: CN1.VBUS, D2.A, JP4.5
VDDCORE: C3.1, IC3.29 (VDDCORE)
VOUT: C1.1, D2.C, D3.C, U1.1 (IN), U1.3 (EN)
~RESET: IC3.26 (/RESET), JP3.5, Q2.A, Q2.A' (P1)

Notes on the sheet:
Adafruit PyRuler
http://adafruit.com/products/4319
CC 2.5 BY-SA
Very bright 0603~{ Use} 10K

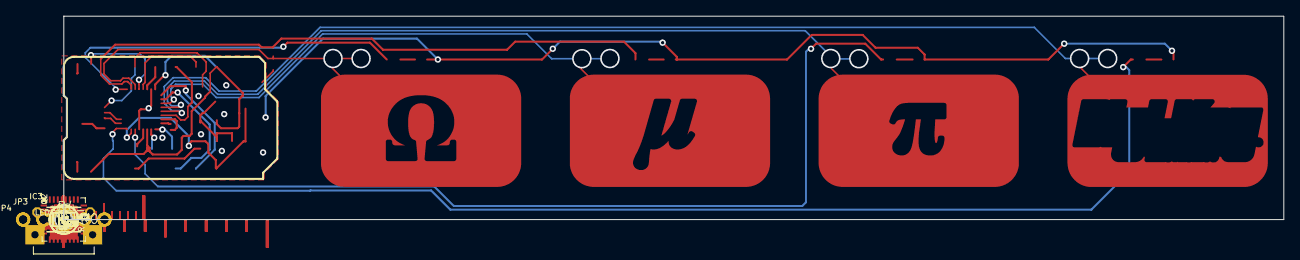
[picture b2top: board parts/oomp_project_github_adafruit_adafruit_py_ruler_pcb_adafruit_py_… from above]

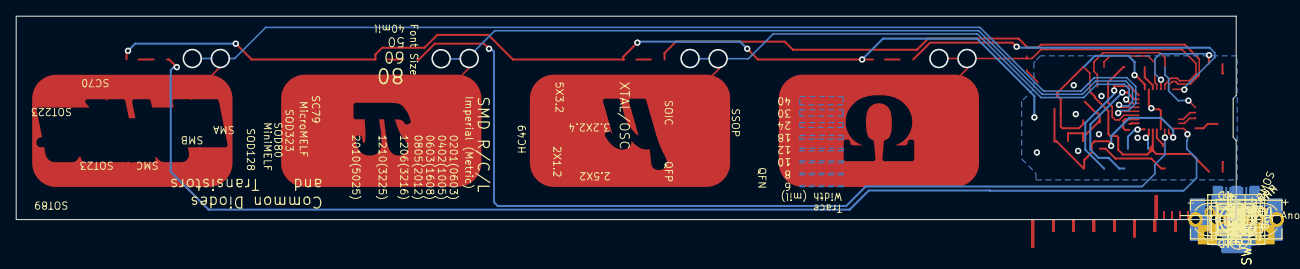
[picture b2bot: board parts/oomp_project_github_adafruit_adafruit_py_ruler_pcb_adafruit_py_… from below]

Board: 16 copper layers, 152.4 x 25.4 mm, 98 parts (43 on the bottom side), 30 nets.

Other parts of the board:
E$1, E$2, E$3, E$4, E$5, E$6, E$7, E$8, E$9, E$10, E$11, E$12, E$13, E$14, E$15: EDGE-MILLIMETERS
E$16, E$60, E$63: 0201
E$17, E$18, E$19, E$20, E$21, E$22: EDGE-INCHES-TENTH
E$23, E$61: 0402
E$24, E$62: 0603
E$25: 0805
E$26: 1206
E$27: 1210
E$28: 2010
E$31: SOT223
E$32: SOT89
E$33: SOT23-5
E$34: SOT23-3
E$35: SC70
E$36: CRYSTAL-SMD-5X3.2
E$37: CRYSTAL-SMD-3.2X2.5
E$38: CRYSTAL-SMD-2.5X2
E$39: HC49UP
E$40: XTAL-2X1.2
E$41: MICROMELF-R
E$42: SC79_INFINEON
E$43: SMA-DIODE
E$44: SMB-DIODE
E$45: SMC
E$47: SOD-128
E$48: SOD-323
E$49: SOD80C
E$50: NMOS-SYMB
E$51: PMOS-SYMB
E$52: DIODE-SYMB
E$53: LED-GUIDE
E$54: NPN-SYMB
E$55: QFN-24
E$56: TSSOP16
E$57: SO08
E$58: TQFP32-5MM
E$59: PNP-SYMB
U$2: PYRULER_BOTTOM
U$7: PCBFEAT-REV-040
U$14: PYRULER_TOP
U$20: TRINKET_M0_TOP
UNK_HOLE_0: dummyfp0
UNK_HOLE_1: dummyfp1

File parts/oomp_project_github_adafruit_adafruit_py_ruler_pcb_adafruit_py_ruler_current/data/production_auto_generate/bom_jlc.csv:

Comment,Designator,Footprint,LCSC Part #
,"E$16,E$60,E$63",Adafruit_PyRuler-import-fps:0201,
,"E$23,E$61",Adafruit_PyRuler-import-fps:0402,
,"E$24,E$62",Adafruit_PyRuler-import-fps:0603,
,E$25,Adafruit_PyRuler-import-fps:0805,
,E$26,Adafruit_PyRuler-import-fps:1206,
,E$27,Adafruit_PyRuler-import-fps:1210,
,"JP3,JP4",Adafruit_PyRuler-import-fps:1X05_ROUND_70,C42431835
,E$28,Adafruit_PyRuler-import-fps:2010,
,E$38,Adafruit_PyRuler-import-fps:CRYSTAL-SMD-2.5X2,
,E$37,Adafruit_PyRuler-import-fps:CRYSTAL-SMD-3.2X2.5,
,E$36,Adafruit_PyRuler-import-fps:CRYSTAL-SMD-5X3.2,
,E$52,Adafruit_PyRuler-import-fps:DIODE-SYMB,
,"E$17,E$18,E$19,E$20,E$21,E$22",Adafruit_PyRuler-import-fps:EDGE-INCHES-TENTH,
,"E$1,E$2,E$3,E$4,E$5,E$6,E$7,E$8,E$9,E$10,E$11,E$12,E$13,E$14,E$15",Adafruit_PyRuler-import-fps:EDGE-MILLIMETERS,
,E$39,Adafruit_PyRuler-import-fps:HC49UP,
,E$53,Adafruit_PyRuler-import-fps:LED-GUIDE,
,E$41,Adafruit_PyRuler-import-fps:MICROMELF-R,
,E$50,Adafruit_PyRuler-import-fps:NMOS-SYMB,
,E$54,Adafruit_PyRuler-import-fps:NPN-SYMB,
,U$7,Adafruit_PyRuler-import-fps:PCBFEAT-REV-040,
,E$51,Adafruit_PyRuler-import-fps:PMOS-SYMB,
,E$59,Adafruit_PyRuler-import-fps:PNP-SYMB,
,U$2,Adafruit_PyRuler-import-fps:PYRULER_BOTTOM,
,U$14,Adafruit_PyRuler-import-fps:PYRULER_TOP,
,E$55,Adafruit_PyRuler-import-fps:QFN-24,
,E$35,Adafruit_PyRuler-import-fps:SC70,
,E$42,Adafruit_PyRuler-import-fps:SC79_INFINEON,
,E$43,Adafruit_PyRuler-import-fps:SMA-DIODE,
,E$44,Adafruit_PyRuler-import-fps:SMB-DIODE,
,E$45,Adafruit_PyRuler-import-fps:SMC,
,E$57,Adafruit_PyRuler-import-fps:SO08,
,E$47,Adafruit_PyRuler-import-fps:SOD-128,
,E$48,Adafruit_PyRuler-import-fps:SOD-323,
,E$49,Adafruit_PyRuler-import-fps:SOD80C,
,E$31,Adafruit_PyRuler-import-fps:SOT223,
,E$34,Adafruit_PyRuler-import-fps:SOT23-3,
,E$33,Adafruit_PyRuler-import-fps:SOT23-5,
,E$32,Adafruit_PyRuler-import-fps:SOT89,
,E$58,Adafruit_PyRuler-import-fps:TQFP32-5MM,
,U$20,Adafruit_PyRuler-import-fps:TRINKET_M0_TOP,
,E$56,Adafruit_PyRuler-import-fps:TSSOP16,
,E$40,Adafruit_PyRuler-import-fps:XTAL-2X1.2,
10K,"R4,R5,R6",Adafruit_PyRuler-import-fps:0603-NO,C98220
10uF,"C1,C8",Adafruit_PyRuler-import-fps:0805-NO,
1uF,"C2,C3",Adafruit_PyRuler-import-fps:0603-NO,C5673
2.2K,"R1,R2,R3",Adafruit_PyRuler-import-fps:0603-NO,C4190
2M,R7,Adafruit_PyRuler-import-fps:0603-NO,
4U#20329,CN1,Adafruit_PyRuler-import-fps:4UCONN_20329_NARROW,
AP102-2020,LED1,Adafruit_PyRuler-import-fps:APA102_2020,
AP2112K-3.3,U1,Adafruit_PyRuler-import-fps:SOT23-5,
ATSAMD21E,IC3,Adafruit_PyRuler-import-fps:QFN32_5MM,
blue,L3,Adafruit_PyRuler-import-fps:CHIPLED_0603_NOOUTLINE,
FIDUCIAL_1MM,"U$1,U$6",Adafruit_PyRuler-import-fps:FIDUCIAL_1MM,
green,"L4,PWR0",Adafruit_PyRuler-import-fps:CHIPLED_0603_NOOUTLINE,
red,"L0,L2",Adafruit_PyRuler-import-fps:CHIPLED_0603_NOOUTLINE,
reset,Q2,Adafruit_PyRuler-import-fps:BTN_KMR2_4.6X2.8,
SCHOTTKY,"D2,D3",Adafruit_PyRuler-import-fps:SOD-123FL,
"TPB1,27","SWC0,SWD0","Adafruit_PyRuler-import-fps:B1,27",
yellow,L1,Adafruit_PyRuler-import-fps:CHIPLED_0603_NOOUTLINE,

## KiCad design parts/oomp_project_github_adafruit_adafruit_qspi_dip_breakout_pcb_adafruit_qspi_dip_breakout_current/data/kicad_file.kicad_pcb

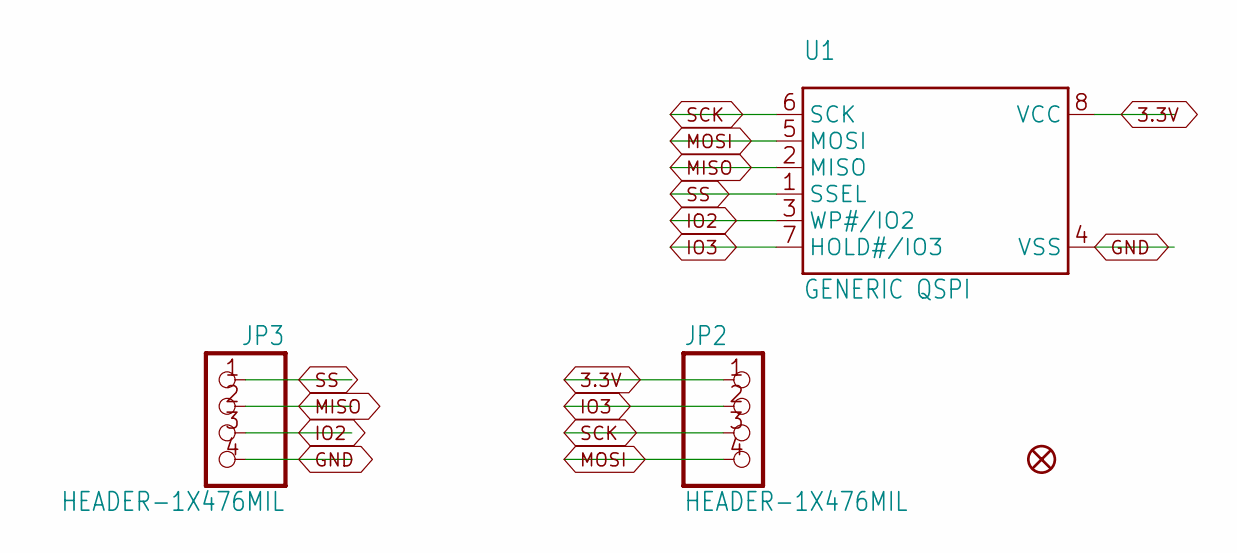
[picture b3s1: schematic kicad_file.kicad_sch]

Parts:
FID1: FIDUCIAL_1MM
JP2, JP3: HEADER-1X476MIL; 1X04_ROUND_76
U1: GENERIC QSPI; SOIC8_208MIL

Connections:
3.3V: JP2.1, U1.8 (VCC)
GND: JP3.4, U1.4 (VSS)
IO2: JP3.3, U1.3 (WP#/IO2)
IO3: JP2.2, U1.7 (HOLD#/IO3)
MISO: JP3.2, U1.2 (MISO)
MOSI: JP2.4, U1.5 (MOSI)
SCK: JP2.3, U1.6 (SCK)
SS: JP3.1, U1.1 (SSEL)

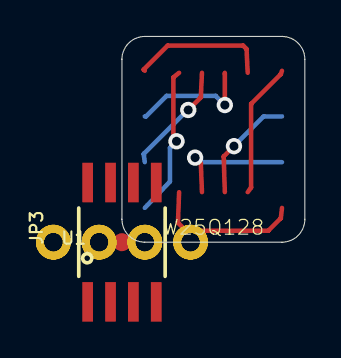
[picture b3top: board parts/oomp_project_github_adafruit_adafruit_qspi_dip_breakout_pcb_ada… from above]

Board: 2 copper layers, 10.2 x 11.4 mm, 5 parts (1 on the bottom side), 8 nets.

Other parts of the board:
U$4: ADAFRUIT_2.5MM

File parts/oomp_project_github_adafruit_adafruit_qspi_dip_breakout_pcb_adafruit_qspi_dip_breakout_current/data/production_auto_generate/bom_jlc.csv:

Comment,Designator,Footprint,LCSC Part #
,"JP2,JP3",Adafruit QSPI DIP Breakout-import-fps:1X04_ROUND_76,C42431795
,U$4,Adafruit QSPI DIP Breakout-import-fps:ADAFRUIT_2.5MM,
GENERIC QSPI,U1,Adafruit QSPI DIP Breakout-import-fps:SOIC8_208MIL,
